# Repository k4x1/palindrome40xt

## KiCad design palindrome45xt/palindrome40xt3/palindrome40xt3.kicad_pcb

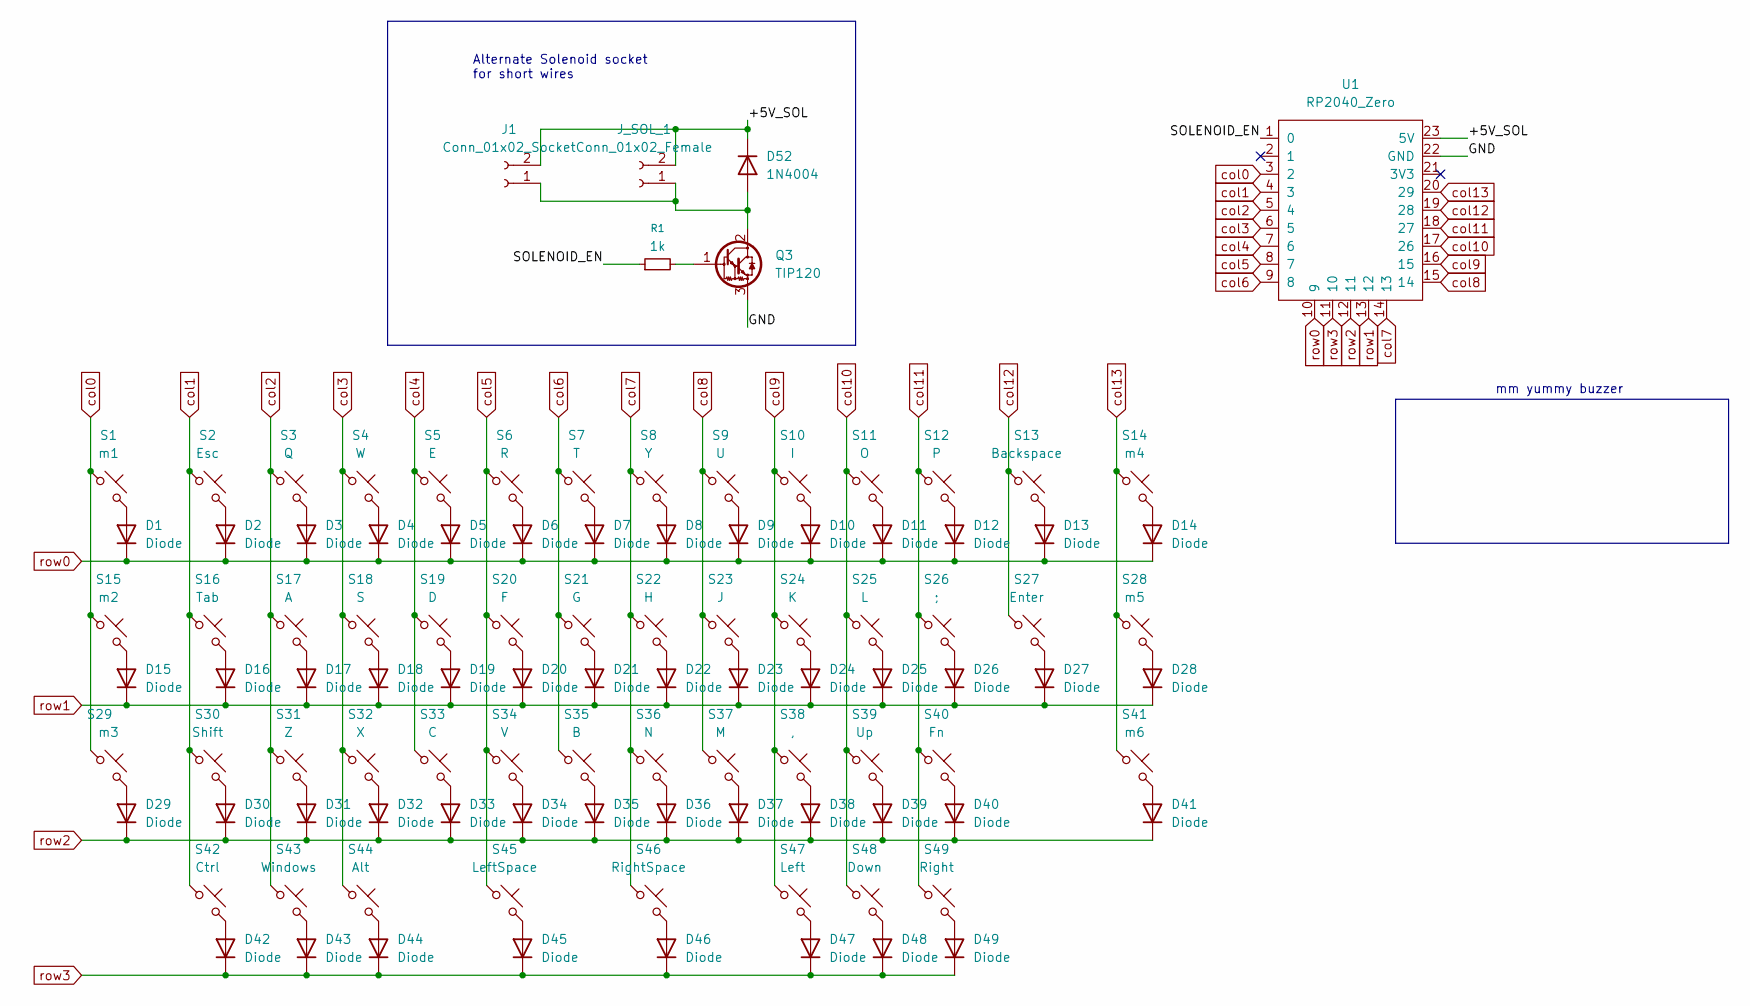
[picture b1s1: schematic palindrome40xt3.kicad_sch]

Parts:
D1, D2, D3, D4, D5, D6, D7, D8, D9, D10, D11, D12, D13, D14, D15, D16, D17, D18, D19, D20, D21, D22, D23, D24, D25, D26, D27, D28, D29, D30, D31, D32, D33, D34, D35, D36, D37, D38, D39, D40, D41, D42, D43, D44, D45, D46, D47, D48, D49: Diode; D_SOD-123
D52: 1N4004; D_DO-41_SOD81_P10.16mm_Horizontal
J1: Conn_01x02_Socket; PinHeader_1x02_P2.54mm_Vertical
J_SOL_1: Conn_01x02_Female; PinHeader_1x02_P2.54mm_Vertical
Q3: TIP120; TO-220-3_Horizontal_TabDown_ergodonk_simple_zero
R1: 1k; R_Axial_DIN0309_L9.0mm_D3.2mm_P12.70mm_Horizontal
S1: m1; SW_Cherry_MX_1.00u_PCB
S2: Esc; SW_Cherry_MX_1.00u_PCB
S3: Q; SW_Cherry_MX_1.00u_PCB
S4: W; SW_Cherry_MX_1.00u_PCB
S5: E; SW_Cherry_MX_1.00u_PCB
S6: R; SW_Cherry_MX_1.00u_PCB
S7: T; SW_Cherry_MX_1.00u_PCB
S8: Y; SW_Cherry_MX_1.00u_PCB
S9: U; SW_Cherry_MX_1.00u_PCB
S10: I; SW_Cherry_MX_1.00u_PCB
S11: O; SW_Cherry_MX_1.00u_PCB
S12: P; SW_Cherry_MX_1.00u_PCB
S13: Backspace; SW_Cherry_MX_1.50u_PCB
S14: m4; SW_Cherry_MX_1.00u_PCB
S15: m2; SW_Cherry_MX_1.00u_PCB
S16: Tab; SW_Cherry_MX_1.25u_PCB
S17: A; SW_Cherry_MX_1.00u_PCB
S18: S; SW_Cherry_MX_1.00u_PCB
S19: D; SW_Cherry_MX_1.00u_PCB
S20: F; SW_Cherry_MX_1.00u_PCB
S21: G; SW_Cherry_MX_1.00u_PCB
S22: H; SW_Cherry_MX_1.00u_PCB
S23: J; SW_Cherry_MX_1.00u_PCB
S24: K; SW_Cherry_MX_1.00u_PCB
S25: L; SW_Cherry_MX_1.00u_PCB
S26: ;; SW_Cherry_MX_1.00u_PCB
S27: Enter; SW_Cherry_MX_1.25u_PCB
S28: m5; SW_Cherry_MX_1.00u_PCB
S29: m3; SW_Cherry_MX_1.00u_PCB
S30: Shift; SW_Cherry_MX_1.75u_PCB
S31: Z; SW_Cherry_MX_1.00u_PCB
S32: X; SW_Cherry_MX_1.00u_PCB
S33: C; SW_Cherry_MX_1.00u_PCB
S34: V; SW_Cherry_MX_1.00u_PCB
S35: B; SW_Cherry_MX_1.00u_PCB
S36: N; SW_Cherry_MX_1.00u_PCB
S37: M; SW_Cherry_MX_1.00u_PCB
S38: ,; SW_Cherry_MX_1.00u_PCB
S39: Up; SW_Cherry_MX_1.00u_PCB
S40: Fn; SW_Cherry_MX_1.75u_PCB
S41: m6; SW_Cherry_MX_1.00u_PCB
S42: Ctrl; SW_Cherry_MX_1.00u_PCB
S43: Windows; SW_Cherry_MX_1.00u_PCB
S44: Alt; SW_Cherry_MX_1.00u_PCB
S45: LeftSpace; SW_Cherry_MX_2.25u_PCB
S46: RightSpace; SW_Cherry_MX_2.75u_PCB
S47: Left; SW_Cherry_MX_1.00u_PCB
S48: Down; SW_Cherry_MX_1.00u_PCB
S49: Right; SW_Cherry_MX_1.00u_PCB
U1: RP2040_Zero

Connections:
/+5V_SOL: D52.1 (K), J1.2, J_SOL_1.2, U1.23 (5V)
/GND: Q3.3 (E), U1.22 (GND)
/SOLENOID_EN: R1.1, U1.1 (0)
unnamed: D1.2 (A), S1.2
unnamed: D2.2 (A), S2.2
unnamed: D3.2 (A), S3.2
unnamed: D4.2 (A), S4.2
unnamed: D5.2 (A), S5.2
unnamed: D6.2 (A), S6.2
unnamed: D7.2 (A), S7.2
unnamed: D9.2 (A), S9.2
unnamed: D10.2 (A), S10.2
unnamed: D11.2 (A), S11.2
unnamed: D12.2 (A), S12.2
unnamed: D13.2 (A), S13.2
unnamed: D14.2 (A), S14.2
unnamed: D15.2 (A), S15.2
unnamed: D16.2 (A), S16.2
unnamed: D17.2 (A), S17.2
unnamed: D18.2 (A), S18.2
unnamed: D19.2 (A), S19.2
unnamed: D20.2 (A), S20.2
unnamed: D21.2 (A), S21.2
unnamed: D22.2 (A), S22.2
unnamed: D23.2 (A), S23.2
unnamed: D24.2 (A), S24.2
unnamed: D25.2 (A), S25.2
unnamed: D26.2 (A), S26.2
unnamed: D27.2 (A), S27.2
unnamed: D28.2 (A), S28.2
unnamed: D29.2 (A), S29.2
unnamed: D30.2 (A), S30.2
unnamed: D31.2 (A), S31.2
unnamed: D32.2 (A), S32.2
unnamed: D33.2 (A), S33.2
unnamed: D34.2 (A), S34.2
unnamed: D35.2 (A), S35.2
unnamed: D36.2 (A), S36.2
unnamed: D37.2 (A), S37.2
unnamed: D38.2 (A), S38.2
unnamed: D39.2 (A), S39.2
unnamed: D40.2 (A), S40.2
unnamed: D41.2 (A), S41.2
unnamed: D42.2 (A), S42.2
unnamed: D43.2 (A), S43.2
unnamed: D44.2 (A), S44.2
unnamed: D45.2 (A), S45.2
unnamed: D46.2 (A), S46.2
unnamed: D47.2 (A), S47.2
unnamed: D48.2 (A), S48.2
unnamed: D49.2 (A), S49.2
unnamed: D52.2 (A), J1.1, J_SOL_1.1, Q3.2 (C)
unnamed: Q3.1 (B), R1.2
Y_KEY: D8.2 (A), S8.2, U1.2 (1)
col0: S1.1, S15.1, S29.1, U1.3 (2)
col1: S2.1, S16.1, S30.1, S42.1, U1.4 (3)
col2: S3.1, S17.1, S31.1, S43.1, U1.5 (4)
col3: S4.1, S18.1, S32.1, S44.1, U1.6 (5)
col4: S5.1, S19.1, S33.1, U1.7 (6)
col5: S6.1, S20.1, S34.1, S45.1, U1.8 (7)
col6: S7.1, S21.1, S35.1, U1.9 (8)
col7: S8.1, S22.1, S36.1, S46.1, U1.14 (13)
col8: S9.1, S23.1, S37.1, U1.15 (14)
col9: S10.1, S24.1, S38.1, S47.1, U1.16 (15)
col10: S11.1, S25.1, S39.1, S48.1, U1.17 (26)
col11: S12.1, S26.1, S40.1, S49.1, U1.18 (27)
col12: S13.1, S27.1, U1.19 (28)
col13: S14.1, S28.1, S41.1, U1.20 (29)
row0: D1.1 (K), D2.1 (K), D3.1 (K), D4.1 (K), D5.1 (K), D6.1 (K), D7.1 (K), D8.1 (K), D9.1 (K), D10.1 (K), D11.1 (K), D12.1 (K), D13.1 (K), D14.1 (K), U1.10 (9)
row1: D15.1 (K), D16.1 (K), D17.1 (K), D18.1 (K), D19.1 (K), D20.1 (K), D21.1 (K), D22.1 (K), D23.1 (K), D24.1 (K), D25.1 (K), D26.1 (K), D27.1 (K), D28.1 (K), U1.13 (12)
row2: D29.1 (K), D30.1 (K), D31.1 (K), D32.1 (K), D33.1 (K), D34.1 (K), D35.1 (K), D36.1 (K), D37.1 (K), D38.1 (K), D39.1 (K), D40.1 (K), D41.1 (K), U1.12 (11)
row3: D42.1 (K), D43.1 (K), D44.1 (K), D45.1 (K), D46.1 (K), D47.1 (K), D48.1 (K), D49.1 (K), U1.11 (10)

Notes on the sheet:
Alternate Solenoid socket for short wires
mm yummy buzzer

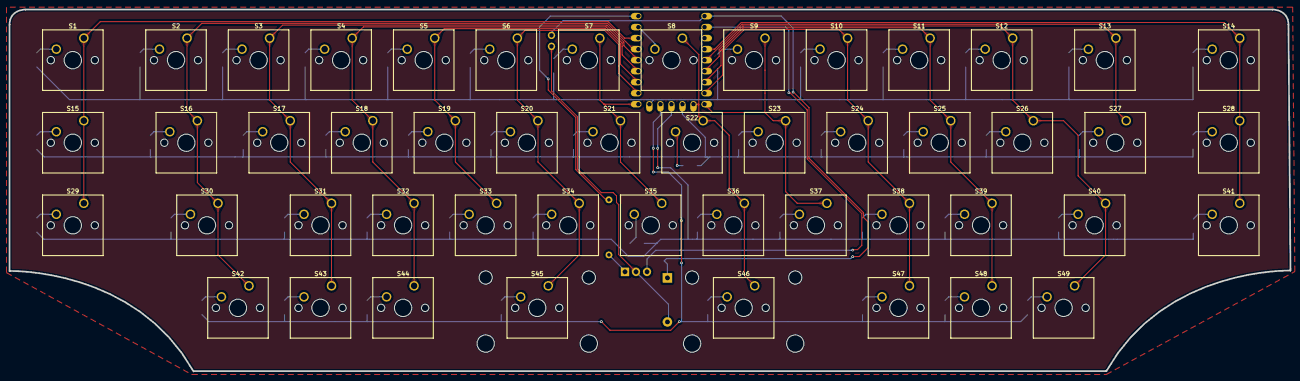
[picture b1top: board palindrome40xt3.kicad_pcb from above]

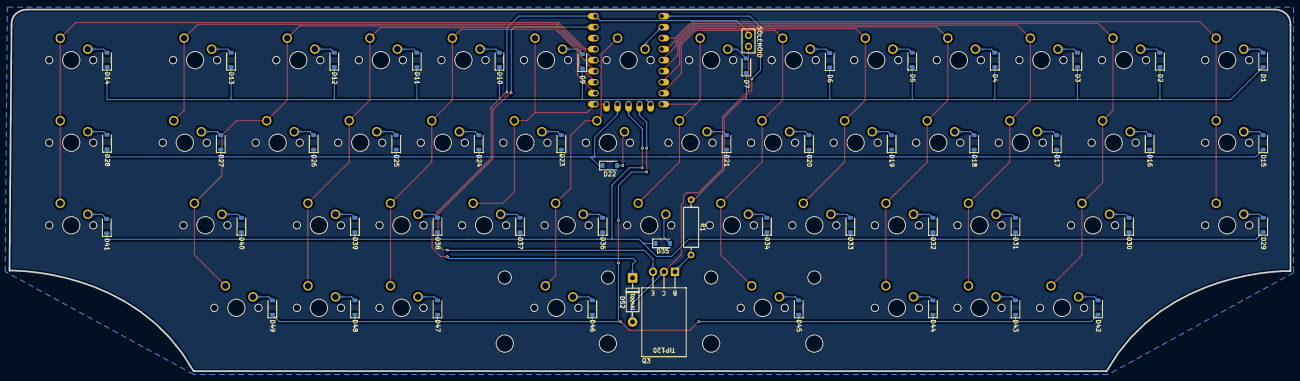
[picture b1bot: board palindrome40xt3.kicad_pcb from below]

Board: 2 copper layers, 295.5 x 83.5 mm, 102 parts (53 on the bottom side), 72 nets.

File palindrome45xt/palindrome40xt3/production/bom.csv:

Designator,Footprint,Quantity,Value,LCSC Part #
"D1, D10, D11, D12, D13, D14, D15, D16, D17, D18, D19, D2, D20, D21, D22, D23, D24, D25, D26, D27, D28, D29, D3, D30, D31, D32, D33, D34, D35, D36, D37, D38, D39, D4, D40, D41, D42, D43, D44, D45, D46, D47, D48, D49, D5, D6, D7, D9",D_SOD-123,48,Diode,
D52,D_DO-41_SOD81_P10.16mm_Horizontal,1,1N4004,
J_SOL_1,PinHeader_1x02_P2.54mm_Vertical,1,Conn_01x02_Female,
Q3,TO-220-3_Horizontal_TabDown_ergodonk_simple_zero,1,TIP120,
R1,R_Axial_DIN0309_L9.0mm_D3.2mm_P12.70mm_Horizontal,1,1k,
S1,SW_Cherry_MX_1.00u_PCB,1,m1,
S10,SW_Cherry_MX_1.00u_PCB,1,I,
S11,SW_Cherry_MX_1.00u_PCB,1,O,
S12,SW_Cherry_MX_1.00u_PCB,1,P,
S13,SW_Cherry_MX_1.50u_PCB,1,Backspace,
S14,SW_Cherry_MX_1.00u_PCB,1,m4,
S15,SW_Cherry_MX_1.00u_PCB,1,m2,
S16,SW_Cherry_MX_1.25u_PCB,1,Tab,
S17,SW_Cherry_MX_1.00u_PCB,1,A,
S18,SW_Cherry_MX_1.00u_PCB,1,S,
S19,SW_Cherry_MX_1.00u_PCB,1,D,
S2,SW_Cherry_MX_1.00u_PCB,1,Esc,
S20,SW_Cherry_MX_1.00u_PCB,1,F,
S21,SW_Cherry_MX_1.00u_PCB,1,G,
S22,SW_Cherry_MX_1.00u_PCB,1,H,
S23,SW_Cherry_MX_1.00u_PCB,1,J,
S24,SW_Cherry_MX_1.00u_PCB,1,K,
S25,SW_Cherry_MX_1.00u_PCB,1,L,
S26,SW_Cherry_MX_1.00u_PCB,1,;,
S27,SW_Cherry_MX_1.25u_PCB,1,Enter,
S28,SW_Cherry_MX_1.00u_PCB,1,m5,
S29,SW_Cherry_MX_1.00u_PCB,1,m3,
S3,SW_Cherry_MX_1.00u_PCB,1,Q,
S30,SW_Cherry_MX_1.75u_PCB,1,Shift,
S31,SW_Cherry_MX_1.00u_PCB,1,Z,
S32,SW_Cherry_MX_1.00u_PCB,1,X,
S33,SW_Cherry_MX_1.00u_PCB,1,C,
S34,SW_Cherry_MX_1.00u_PCB,1,V,
S35,SW_Cherry_MX_1.00u_PCB,1,B,
S36,SW_Cherry_MX_1.00u_PCB,1,N,
S37,SW_Cherry_MX_1.00u_PCB,1,M,
S38,SW_Cherry_MX_1.00u_PCB,1,",",
S39,SW_Cherry_MX_1.00u_PCB,1,Up,
S4,SW_Cherry_MX_1.00u_PCB,1,W,
S40,SW_Cherry_MX_1.75u_PCB,1,Fn,
S41,SW_Cherry_MX_1.00u_PCB,1,m6,
S42,SW_Cherry_MX_1.00u_PCB,1,Ctrl,
S43,SW_Cherry_MX_1.00u_PCB,1,Windows,
S44,SW_Cherry_MX_1.00u_PCB,1,Alt,
S45,SW_Cherry_MX_2.25u_PCB,1,LeftSpace,
S46,SW_Cherry_MX_2.75u_PCB,1,RightSpace,
S47,SW_Cherry_MX_1.00u_PCB,1,Left,
S48,SW_Cherry_MX_1.00u_PCB,1,Down,
S49,SW_Cherry_MX_1.00u_PCB,1,Right,
S5,SW_Cherry_MX_1.00u_PCB,1,E,
S6,SW_Cherry_MX_1.00u_PCB,1,R,
S7,SW_Cherry_MX_1.00u_PCB,1,T,
S8,SW_Cherry_MX_1.00u_PCB,1,Y,
S9,SW_Cherry_MX_1.00u_PCB,1,U,
U1,RP2040_Zero,1,RP2040_Zero,

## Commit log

2025-09-09 init comit
2025-09-09 init commit
2025-09-09 upside down version
2025-09-09 almost done
2025-09-09 no more errors
2025-09-09 pre disaster
2025-09-10 before disaster
2025-09-10 disaster here
2025-09-11 rewiring time
2025-09-11 donezo
2025-09-12 firmware done i think
2025-09-14 plate n stuff
2025-09-14 `pre disaster
2025-09-14 2 side gasket version
